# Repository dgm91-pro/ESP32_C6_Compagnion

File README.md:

# ESP32 C6 Project ! 👋

Welcome to my repository. Here you will find every informations you need to build a small esp32 deskbot with usefull features and gadgets that other deskbot does not have.

## Introduction

So what is the ESP32 C6 Project ?

This project is a deskbot , but also a good Classmate and an AI Teacher. 
This project came from a very random idea : i wanted to build something usefull for me and other students , but also something that look's cool and that is easy to carry.
I chose this esp board because i've seen a lot of people using it and i wanted something compact , with good documentations , and with a lot of integrated features.

The main idea of this project is to make a bot that can listen to your teacher in class , and transcript your whole lessons into text or in markdown.
This idea came to me since i started working on a computer at school , because it's very difficult to stay attentive and you easilly manage to miss some important thing the teacher might say to you.
With this little gadget , you'll never be afraid of missing a part of your lessons and will be performing in class !

## How it Works ?

> [!NOTE]
>  _The Overall Project is in current developpement and some things may change with time , stay tuned !_

This project work with a custom pcb board and a waveshare dev board that both includes different features :

- A Gyroscope
- An SD card reader
- An USB interface
- A Tactile Screen
- Some Audio Output and Input Components
- A Physical button because it's always better to feel things !

Normally , i should use all of those features in this project : 

 - i want to use the audio for AI assistant and listen to teacher ,
 - the sd card might be used to save audio file on it or for the display , 
 - the gyroscope will be to interact with the bot to make some animations , 
 - usb interface should be used to transfert file from sd card , flash and program the esp32 , and even maybe emulate an HID device to write directly like a keyboard.
 - The tactile screen will be showing the bot eyes , battery and maybe a spotify or audio integration , settings etc.
 - tactical button will be used to start and stop recording , power On/Off device ( deep sleep ) and maybe other features.

The PCB board also include a Battery connector , and a Power Mux , wich will negociate beetween USB-C power and Battery power , this ensure the board does not have any short circuit or problem with power.

## Programmation and Software !

> [!CAUTION]
> Hackclub Please Read This : [README.md](Software/README.md).

IMPORTANT : The esp32 board doesn't had many pins left and the main idea was still to use all of the feature , since the board got an usb port , i used the UART default pins for the I2S audio , and GPIO6 as DOUT for the Microphone.
Here is what you ABSOLUTELY NEED TO DO : 

> Disable the IMU interrupt pin 2 : GPIO6 is used for this purpose as default , but we need to have the audio so , byebye !
> 
> Re-route I2S pin to the default UART pins and disable UART pins : we should not need them.
> 
> Select The USB CDC interface in Arduino IDE

Software will be released as soon as everything is put together !

## Hardware 

### Here is a BOM of the part you need to build ONE board :

Look at : [BOM.csv](BOM.csv) or [BOM.txt](BOM_INFO/BOM.txt)
>[!NOTE]
>In bom.csv there is only the part i need and taxes, parts i have and battery etc will be put in later since i need to try out different batteries , sd etc

_Main Components_

| Qty | Component | In Stock |
|:---:|---|:---:|
| x1 | ESP32-C6 1.47" LCD Touchscreen Board | No |
| x1 | MAX98357A | No |
| x1 | Resistor 1 MΩ | No |
| x2 | Capacitor 220 pF | No |
| x2 | Ferrite Bead ( 100Ω<Independecy at 100Mhz | No |
| x1 | Capacitor 10 µF | No |
| x1 | Capacitor 0.1 µF | No |
| x1 | Resistor 100 kΩ (Optional) | No |
| x1 | SPH0645LM4H | No |
| x1 | Resistor 10 kΩ | No |
| x1 | Resistor 68 Ω | No |
| x1 | Capacitor 1 µF | No |
| x1 | Capacitor 0.1 µF | No |
| x1 | MCP23008 | No |
| x1 | Capacitor 0.1 µF | No |
| x3 | Resistor 470 Ω | No |
| x1 | RGB LED | Yes |
| x1 | Push Button | Yes |
| x1 | TPS2116DRL | No |
| x1 | Resistor 330 kΩ | No |
| x1 | Resistor 100 kΩ | No |

_Additional Components_

| Qty | Component | In Stock |
|:---:|---|:---:|
| x1 | PCB Board | No |
| x1 | SD Card | No |
| x1 | Speaker 8 Ω | Yes |
| x1 | Compatible Battery | Yes |
| x1 | Battery ON/OFF Switch | Yes |

>[!WARNING]
>**Battery Switch:** If no switch is used, the two pads can simply be bridged with a jumper.
>
>**SD Card Safety:** Be careful to remove any power source before working with the SD card.
>
>**3D Model:** For now the 3D model doesn't exist since i need to try different batteries , but you'll need to adapt it if you don't use the one i'll select.
>
>**Audio Gain:** The 100 kΩ resistor for gain tuning is optional, and you can jump it or leave it without.

## 3D Model and Parts 

> [!CAUTION]
> Hackclub Please Read This : [README.md](CAD/README.md).

In the CAD folder , you'll find a .step file of the whole pcb with every components execpt the MAX98570 but it's not really harmfull.
3d parts are Comming , please wait until i can actually mesure the real size of the board and the battery i'm gonna be using etc...

### Some Pictures Of This Project ! 

( UPDATED )

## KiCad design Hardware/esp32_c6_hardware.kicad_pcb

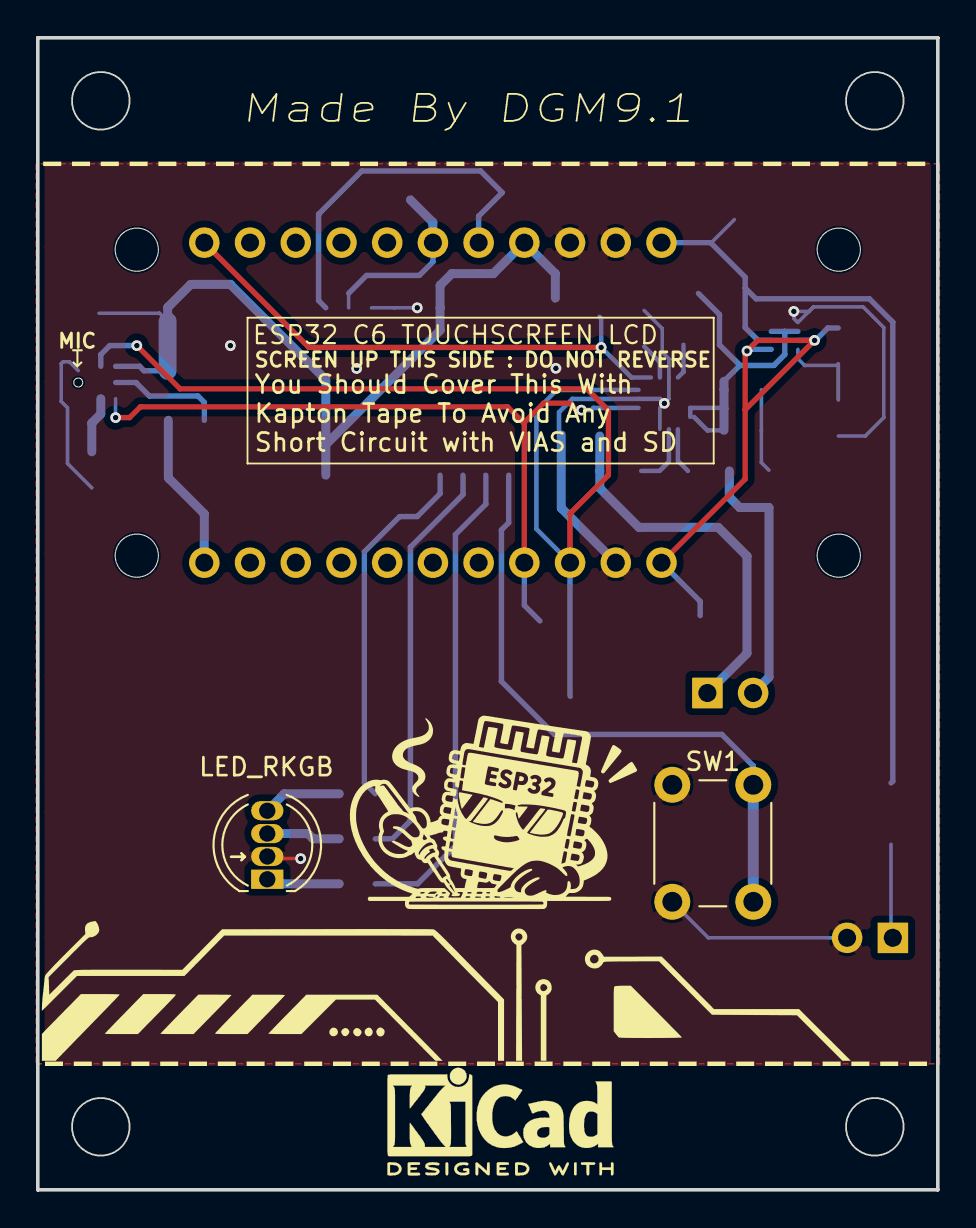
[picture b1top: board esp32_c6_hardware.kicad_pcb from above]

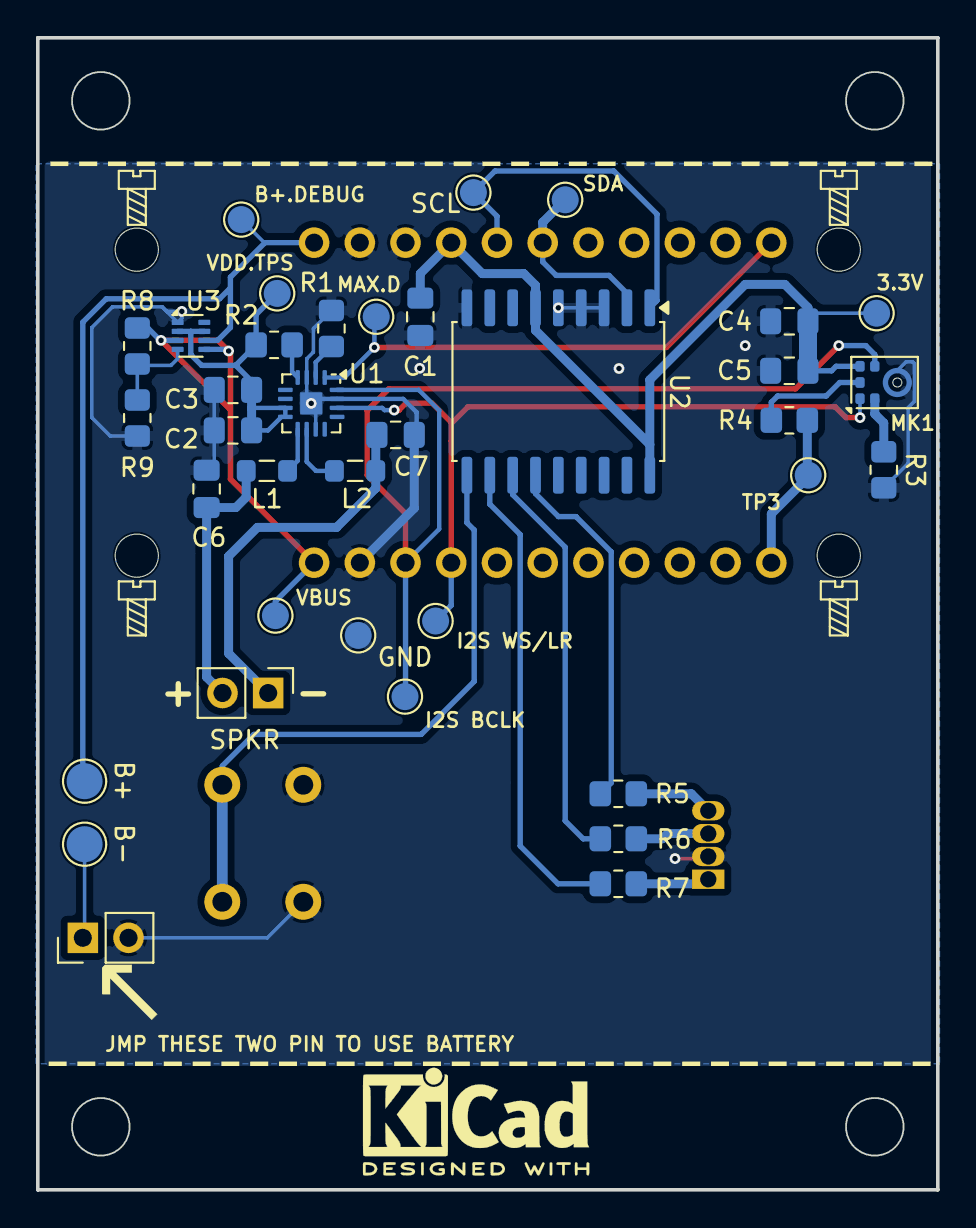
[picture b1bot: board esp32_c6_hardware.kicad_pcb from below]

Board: 2 copper layers, 50.0 x 64.0 mm, 41 parts (37 on the bottom side), 28 nets.

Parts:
3.3V: 3V3; TestPoint_Pad_D1.5mm
B+: BATTERY +; TestPoint_Pad_D2.0mm
B+.DEBUG: VBAT; TestPoint_Pad_D1.5mm
B-: BATTERY -; TestPoint_Pad_D2.0mm
C1, C3, C4: 0.1uF; C_0805_2012Metric_Pad1.18x1.45mm_HandSolder
C2: 10uF; C_0805_2012Metric_Pad1.18x1.45mm_HandSolder
C5: 1uF; C_0805_2012Metric_Pad1.18x1.45mm_HandSolder
C6, C7: 220pF; C_0805_2012Metric_Pad1.18x1.45mm_HandSolder
D1: LED_RKGB; LED_D5.0mm-4_RGB
DGM9.1: LOGO; Logo1
ESP32 C6 TOUCHSCREEN LCD: ESP32-C6-LCD-TOUCH; ESP32-C6-LCD-TOUCH-FOOTPRINT
GND: GND; TestPoint_Pad_D1.5mm
I2S BCLK: I2S_BCLK_DEBUG; TestPoint_Pad_D1.5mm
I2S WS/LR: I2S_LRCLK/WS_DEBUG; TestPoint_Pad_D1.5mm
JMP THESE TWO PIN TO USE BATTERY: BATTERY_JMP; PinHeader_1x02_P2.54mm_Vertical
L1: 100Mhz Independency>100Ω| At Least 1.5A; L_0805_2012Metric_Pad1.05x1.20mm_HandSolder
L2: L_Ferrite; L_0805_2012Metric_Pad1.05x1.20mm_HandSolder
MAX.D: MAX98357A_DIN_DEBUG; TestPoint_Pad_D1.5mm
MK1: SPH0645LM4H; Knowles_SPH0645LM4H-6_3.5x2.65mm
R1: 9db Open / 12 db Close / 15db 100K R; R_0805_2012Metric_Pad1.20x1.40mm_HandSolder
R2: 1MΩ; R_0805_2012Metric_Pad1.20x1.40mm_HandSolder
R3: 10KΩ; R_0805_2012Metric_Pad1.20x1.40mm_HandSolder
R4: 68Ω; R_0805_2012Metric_Pad1.20x1.40mm_HandSolder
R5, R6, R7: 470Ω; R_0805_2012Metric_Pad1.20x1.40mm_HandSolder
R8: 330KΩ; R_0805_2012Metric_Pad1.20x1.40mm_HandSolder
R9: 100KΩ; R_0805_2012Metric_Pad1.20x1.40mm_HandSolder
SCL: SCL_DEBUG; TestPoint_Pad_D1.5mm
SDA: SDA_DEBUG; TestPoint_Pad_D1.5mm
SPKR: OUTPUT AUDIO; PinHeader_1x02_P2.54mm_Vertical
SW1: SW_Push; SW_PUSH_6mm_H4.3mm
TP3: MIC_DOUT_DEBUG; TestPoint_Pad_D1.5mm
U1: MAX98357A; TQFN-16-1EP_3x3mm_P0.5mm_EP1.23x1.23mm
U2: MCP23008-xSO; SOIC-18W_7.5x11.6mm_P1.27mm
U3: TPS2116DRL; SOT-583-8
VBUS: VBUS; TestPoint_Pad_D1.5mm
VDD.TPS: VDD ( TPS_OUT ); TestPoint_Pad_D1.5mm

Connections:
+3.3V: 3.3V.1 (1_1), C1.1, C4.1, C5.1, ESP32 C6 TOUCHSCREEN LCD.15 (3V3), MK1.5 (VDD), U2.6 (~RESET), U2.18 (VDD)
+BATT: B+.1 (1_1), B+.DEBUG.1 (1_1), ESP32 C6 TOUCHSCREEN LCD.12 (VBAT), U3.6 (VIN2)
/I2C_ESP_SCL: ESP32 C6 TOUCHSCREEN LCD.16 (GPIO_19), SCL.1 (1_1), U2.1 (SCL)
/I2C_ESP_SDA: ESP32 C6 TOUCHSCREEN LCD.17 (GPIO_18), SDA.1 (1_1), U2.2 (SDA)
/I2S_BCLK: ESP32 C6 TOUCHSCREEN LCD.9 (GPIO_16), I2S BCLK.1 (1_1), MK1.4 (BCLK), U1.16 (BCLK)
/I2S_LRCLK/WS: ESP32 C6 TOUCHSCREEN LCD.8 (GPIO_17), I2S WS/LR.1 (1_1), MK1.1 (WS), U1.14 (LRCLK)
/MAX98357A_DIN: ESP32 C6 TOUCHSCREEN LCD.22 (GPIO_7), MAX.D.1 (1_1), U1.1 (DIN)
/MIC_DATA: ESP32 C6 TOUCHSCREEN LCD.1 (GPIO_6), R4.2, TP3.1 (1_1)
GND: C1.2, C2.1, C3.1, C4.2, C5.2, C6.1, C7.1, D1.2 (K), ESP32 C6 TOUCHSCREEN LCD.10 (GND), ESP32 C6 TOUCHSCREEN LCD.13 (GND), ESP32 C6 TOUCHSCREEN LCD.14 (GND), GND.1 (1_1), JMP THESE TWO PIN TO USE BATTERY.2, MK1.3 (GND), R1.1, R3.1, R9.1, SW1.2, U1.3 (GND), U1.11 (GND), U1.15 (GND), U1.17 (PAD), U2.3 (A2), U2.4 (A1), U2.5 (A0), U2.9 (VSS), U3.1 (GND)
unnamed: D1.4 (BA), R5.2
unnamed: D1.3 (GA), R6.2
unnamed: D1.1 (RA), R7.2
unnamed: C7.2, L2.2, SPKR.1
unnamed: C6.2, L1.2, SPKR.2
unnamed: B-.1 (1_1), JMP THESE TWO PIN TO USE BATTERY.1
unnamed: MK1.6 (DATA), R4.1
unnamed: MK1.2 (SEL), R3.2
unnamed: R1.2, U1.2 (GAIN_SLOT)
unnamed: L2.1, U1.10 (OUTN)
unnamed: L1.1, U1.9 (OUTP)
unnamed: R2.2, U1.4 (~SD_MODE)
unnamed: SW1.1, U2.10 (GP0)
unnamed: R7.1, U2.11 (GP1)
unnamed: R6.1, U2.12 (GP2)
unnamed: R5.1, U2.13 (GP3)
unnamed: R8.1, R9.2, U3.4 (PR1)
VBUS: ESP32 C6 TOUCHSCREEN LCD.11 (VBUS), R8.2, U3.3 (VIN1), U3.5 (MODE), VBUS.1 (1_1)
VDD: C2.2, C3.2, R2.1, U1.7 (VDD), U1.8 (VDD), U3.2 (VOUT), U3.7 (VOUT), VDD.TPS.1 (1_1)
